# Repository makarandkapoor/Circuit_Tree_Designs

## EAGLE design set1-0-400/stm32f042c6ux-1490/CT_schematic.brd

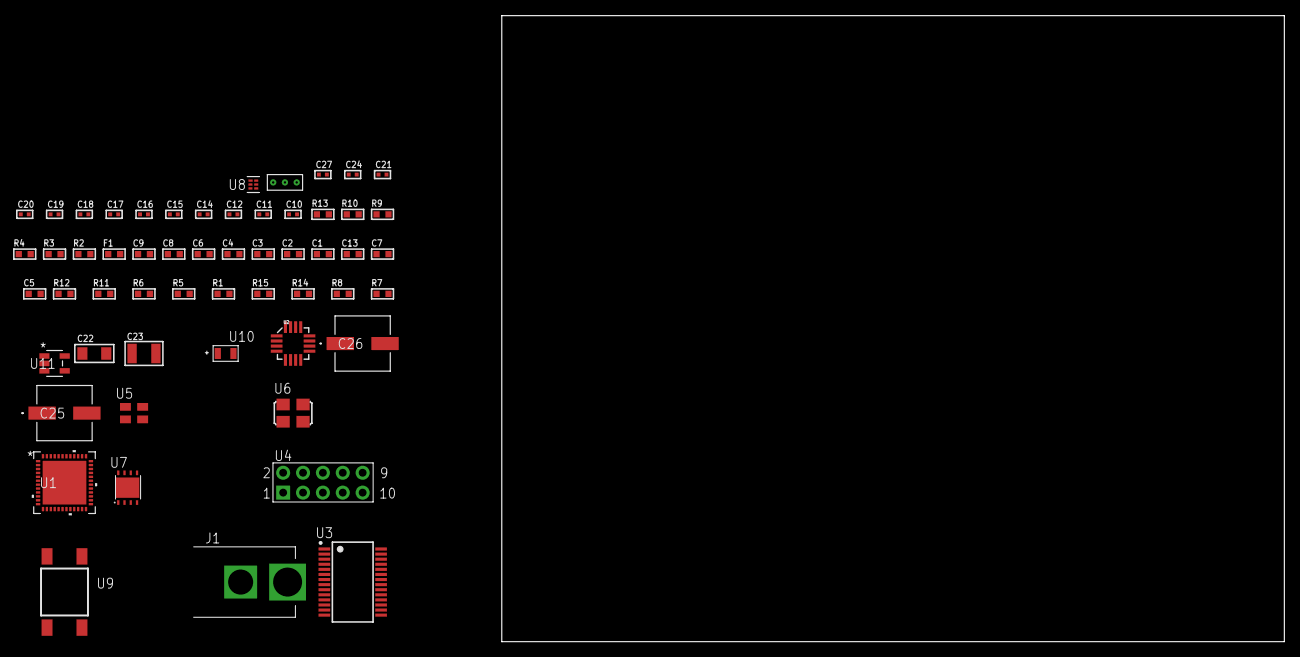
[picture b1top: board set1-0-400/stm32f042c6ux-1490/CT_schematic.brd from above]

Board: 2 copper layers, 100.0 x 80.0 mm, 56 parts (0 on the bottom side), 38 nets, no tracks yet.

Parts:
C1, C9: 1e-06; C0603
C2, C3, C4, C6: 1e-07; C0603
C5, C7: 4.7e-06; C0603
C8: 1e-08; C0603
C10, C11, C12, C19, C20, C21, C27: 1e-08; C0402
C13: 4.7e-07; C0603
C14, C15, C16, C17, C18, C24: 1e-07; C0402
C22: 1e-05; C1206
C23: 1e-05; C1210
C25, C26: 0.0001; EXV-9H
F1: 240.0; L0603
J1: PJ-037B; PJ-037B_PACKAGE
R1, R5, R6, R11, R12: 10000.0; R0603
R2, R10: 1000.0; R0603
R3: 1600.5; R0603
R4: 4700.0; R0603
R7, R8: 100000.0; R0603
R9: 2231.0; R0603
R13: 9100.0; R0603
R14: 680000.0; R0603
R15: 120000.0; R0603
U1: stm32f042c6u6; UFQFPN48
U2: l3g4200d; LGA-16
U3: ST3241EBPR; SSOP-28
U4: HTSS-105-01-G-D
U5: ASEK-32.768KHz-ECST; ASEK
U6: ASFL1-25MHZ-NCS; ASFL1
U7: LP3878SDX-ADJ/NOPB; WSON-8
U8: TPS3895ADRYR; SON-6
U9: 4-1437565-2; SW_4-1437565-2
U10: Q65110A2395; LGM67K-G1J2-24-Z
U11: nc7sz125m5x; NC7SZ125M5X
U12: Dummy; DUMMY_PACKAGE_122

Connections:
CLK_U1_3: U1.3, U5.3
CLK_U1_5: U1.5, U6.3
GND: C1.2, C2.2, C3.2, C4.2, C5.2, C6.2, C7.2, C8.2, C9.2, C10.2, C11.2, C12.2, C14.2, C17.2, C18.2, C19.2, C20.2, C21.2, C22.2, C23.2, C24.2, C25.2, C26.2, C27.2, J1.2, R2.2, R5.1, R5.2, R10.2, R13.2, R15.2, U1.8, U1.23, U1.35, U1.47, U1.49, U2.8, U2.9, U2.10, U2.11, U2.12, U2.13, U3.23, U3.25, U4.9, U5.2, U6.2, U7.3, U7.PAD, U8.2, U10.C, U11.1, U11.3, U12.1
NET_U1_7: R4.1, U1.7, U11.4
NET_U1_9: C8.1, C9.1, F1.1, U1.9
NET_U1_45: R3.1, U1.45, U10.A
NET_U1_46: R1.1, U1.46, U9.3, U9.4
NET_U2_14: C12.1, C13.1, U2.14
NET_U3_1: C16.1, U3.1
NET_U3_2: C16.2, U3.2
NET_U3_3: C18.1, U3.3
NET_U3_22: R7.1, U3.22
NET_U3_24: C15.2, U3.24
NET_U3_27: C17.1, U3.27
NET_U3_28: C15.1, U3.28
NET_U4_3: U3.4, U4.3
NET_U4_4: U3.5, U4.4
NET_U4_5: U3.9, U4.5
NET_U4_6: U3.10, U4.6
NET_U7_1: C21.1, U7.1
NET_U7_6: R9.2, R10.1, U7.6
NET_U7_8: R8.1, U7.8
NET_U8_1: R12.1, R13.1, U8.1
NET_U8_3: R14.2, R15.1, U8.3
NET_U8_4: R11.1, U8.4, U11.2
NET_U9_1: R2.1, U9.1, U9.2
PROC_SPI1_MISO: U1.16, U2.4
PROC_SPI1_MOSI: U1.17, U2.3
PROC_SPI1_NSS: R6.1, U1.14, U2.5
PROC_SPI1_SCK: U1.15, U2.2
PROC_TIM1_CH1: U1.29, U12.3
PROC_TIM1_CH2N: U1.18, U12.2
PROC_USART1_CTS: U1.32, U3.13
PROC_USART1_RTS: U1.33, U3.18
PROC_USART1_RX: U1.31, U3.19
PROC_USART1_TX: U1.30, U3.14
VCC_S1_8V6: C22.1, C25.1, C26.1, J1.1, R8.2, U7.4
VCC_TIER1_3V3: C1.1, C2.1, C3.1, C4.1, C5.1, C6.1, C7.1, C10.1, C11.1, C14.1, C19.1, C20.1, C23.1, C24.1, C27.1, F1.2, R1.2, R3.2, R4.2, R6.2, R7.2, R9.1, R11.2, R12.2, R14.1, U1.1, U1.24, U1.36, U1.48, U2.1, U2.15, U2.16, U3.26, U5.4, U6.4, U7.5, U8.6, U11.5

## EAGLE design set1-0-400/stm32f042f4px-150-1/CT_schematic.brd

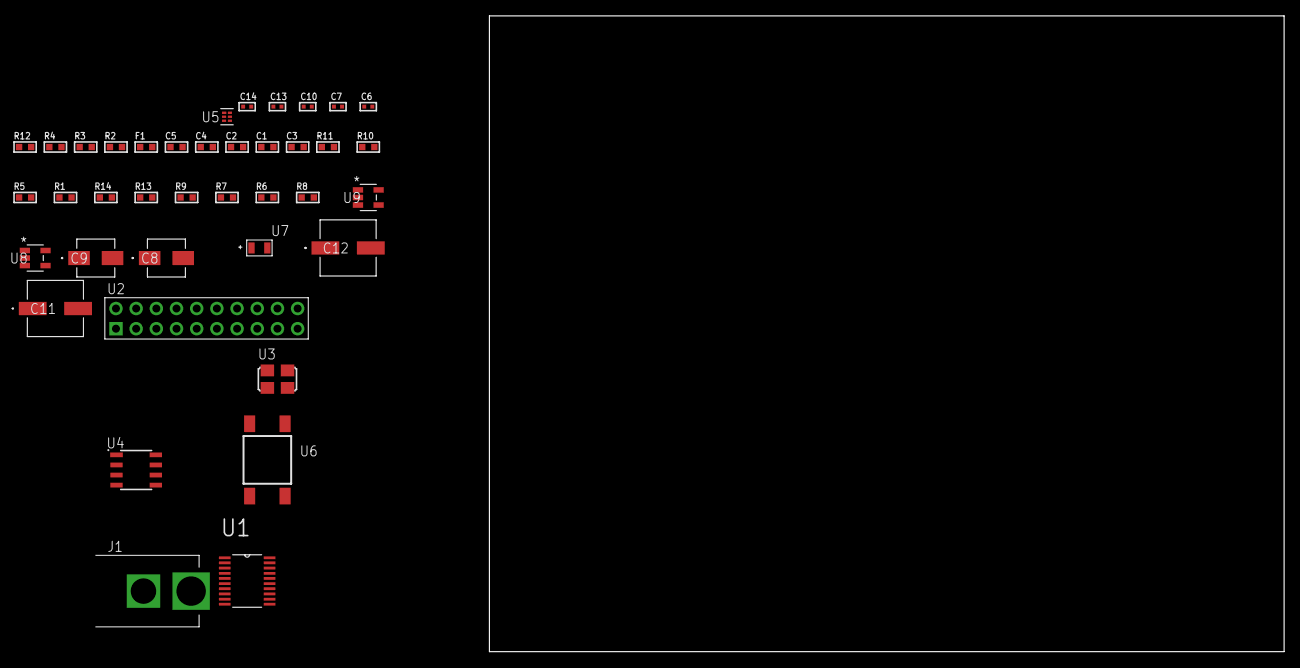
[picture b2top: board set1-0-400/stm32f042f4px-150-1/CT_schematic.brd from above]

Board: 2 copper layers, 100.0 x 80.0 mm, 39 parts (0 on the bottom side), 18 nets, no tracks yet.

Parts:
C1, C2: 1e-07; C0603
C3: 4.7e-06; C0603
C4: 1e-08; C0603
C5: 1e-06; C0603
C6, C10: 1e-07; C0402
C7, C13, C14: 1e-08; C0402
C8: 1e-06; EXV-9B
C9: 2.2e-06; EXV-9B
C11, C12: 0.0001; EXV-9H
F1: 240.0; L0603
J1: PJ-037B; PJ-037B_PACKAGE
R1, R5, R10, R11: 10000.0; R0603
R2: 1000.0; R0603
R3: 1600.5; R0603
R4: 4700.0; R0603
R6, R7, R9: 100000.0; R0603
R8: 164658.62; R0603
R12: 9100.0; R0603
R13: 680000.0; R0603
R14: 120000.0; R0603
U1: stm32f042f4p7; TSSOP20
U2: TST-110-05-T-D-RA
U3: ASFL1-25MHZ-NCS; ASFL1
U4: LP2954AIMX/NOPB; LP2954
U5: TPS3895ADRYR; SON-6
U6: 4-1437565-2; SW_4-1437565-2
U7: Q65110A2395; LGM67K-G1J2-24-Z
U8, U9: nc7sz125m5x; NC7SZ125M5X

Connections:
CLK_U1_2: U1.2, U3.3
GND: C1.2, C2.2, C3.2, C4.2, C5.2, C6.2, C7.2, C8.2, C9.2, C10.2, C11.2, C12.2, C13.2, C14.2, J1.2, R2.2, R9.2, R12.2, R14.2, U1.15, U2.4, U2.6, U2.8, U2.10, U2.12, U2.14, U2.16, U2.18, U2.20, U3.2, U4.4, U5.2, U7.C, U8.2, U8.3, U9.1, U9.3
NET_U1_4: R4.1, U1.4, U9.4
NET_U1_5: C4.1, C5.1, F1.1, U1.5
NET_U1_17: R3.1, U1.17, U7.A
NET_U1_18: R1.1, U1.18, U6.3, U6.4
NET_U4_3: R7.1, U4.3
NET_U4_5: R6.1, U4.5
NET_U4_7: R8.2, R9.1, U4.7
NET_U5_1: R11.1, R12.1, U5.1
NET_U5_3: R13.2, R14.1, U5.3
NET_U5_4: R10.1, U5.4, U8.4, U9.2
NET_U6_1: R2.1, U6.1, U6.2
PROC_SYS_SWCLK: U1.20, U2.9
PROC_SYS_SWDIO: U1.19, U2.7
RST_OUT_U2_SRESET_B: R5.1, U2.15, U8.1
VCC_S1_8V6: C8.1, C11.1, C12.1, J1.1, R7.2, U4.8
VCC_TIER1_3V3: C1.1, C2.1, C3.1, C6.1, C7.1, C9.1, C10.1, C13.1, C14.1, F1.2, R1.2, R3.2, R4.2, R5.2, R6.2, R8.1, R10.2, R11.2, R13.1, U1.16, U2.1, U3.4, U4.1, U5.6, U8.5, U9.5

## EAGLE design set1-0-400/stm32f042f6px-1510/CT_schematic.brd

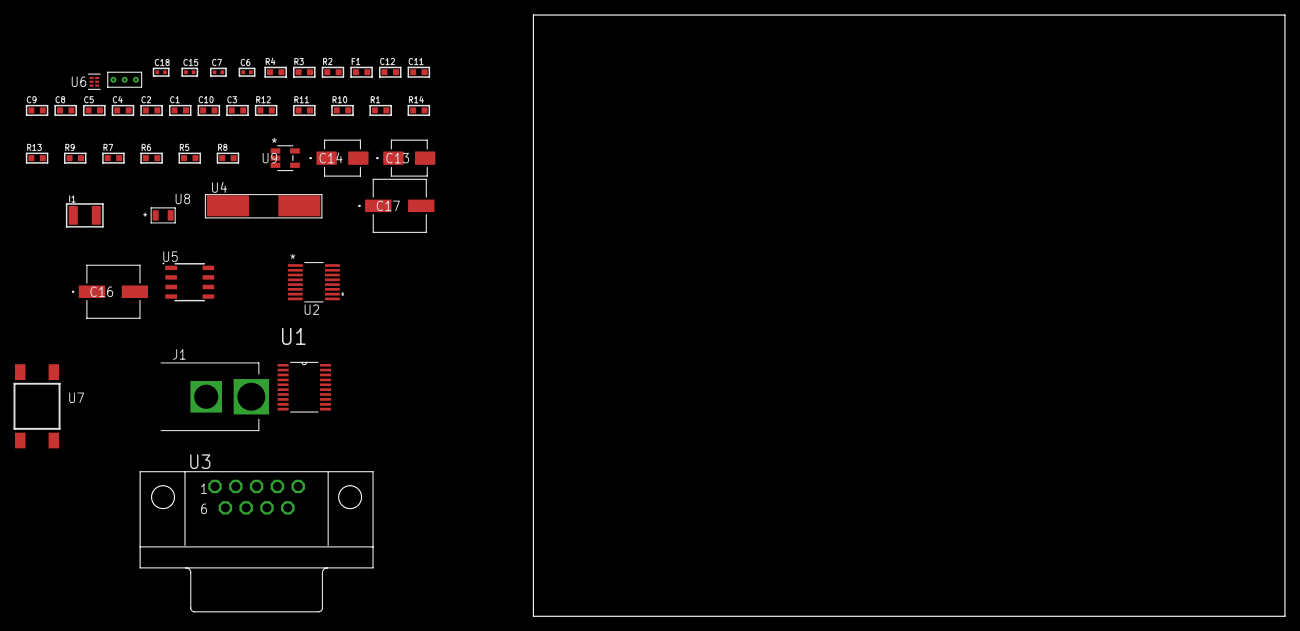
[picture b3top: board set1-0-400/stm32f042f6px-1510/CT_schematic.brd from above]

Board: 2 copper layers, 100.0 x 80.0 mm, 45 parts (0 on the bottom side), 29 nets, no tracks yet.

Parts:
C1, C2: 1e-07; C0603
C3: 4.7e-06; C0603
C4: 1e-08; C0603
C5, C8, C9, C11, C12: 1e-06; C0603
C6, C7: 1e-11; C0402
C10: 2.2e-07; C0603
C13: 1e-06; EXV-9B
C14: 2.2e-06; EXV-9B
C15: 1e-07; C0402
C16, C17: 0.0001; EXV-9H
C18: 1e-08; C0402
F1: 240.0; L0603
I1: 1e-05; L1210
J1: PJ-037B; PJ-037B_PACKAGE
R1, R10, R11: 10000.0; R0603
R2: 1000.0; R0603
R3: 1270.0; R0603
R4: 4700.0; R0603
R5, R6, R7, R9: 100000.0; R0603
R8: 101022.32; R0603
R12: 18000.0; R0603
R13: 470000.0; R0603
R14: 120000.0; R0603
U1: stm32f042f6p7; TSSOP20
U2: LTC2804CGN-1#PBF; SSOP-16
U3: 182-009-113R531; 182-009-MALE
U4: ABLS-25.000MHZ-B2F-T
U5: LP2954AIMX/NOPB; LP2954
U6: TPS3895ADRYR; SON-6
U7: 4-1437565-2; SW_4-1437565-2
U8: Q65110A2395; LGM67K-G1J2-24-Z
U9: nc7sz125m5x; NC7SZ125M5X
U10: Dummy; DUMMY_PACKAGE_89

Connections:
CLK_CRYSTAL_U1_2: C6.1, U1.2, U4.1
CLK_CRYSTAL_U1_3: C7.1, U1.3, U4.2
GND: C1.2, C2.2, C3.2, C4.2, C5.2, C6.2, C7.2, C8.2, C9.2, C11.2, C12.2, C13.2, C14.2, C15.2, C16.2, C17.2, C18.2, J1.2, R2.2, R9.2, R12.2, R14.2, U1.15, U2.8, U3.5, U5.4, U6.2, U8.C, U9.1, U9.3, U10.1
NET_U1_4: R4.1, U1.4, U9.4
NET_U1_5: C4.1, C5.1, F1.1, U1.5
NET_U1_19: R3.1, U1.19, U8.A
NET_U1_20: R1.1, U1.20, U7.3, U7.4
NET_U2_6: C8.1, U2.6
NET_U2_7: C10.1, I1.2, U2.7
NET_U2_9: C9.1, U2.9
NET_U2_10: C10.2, U2.10
NET_U2_11: R5.1, U2.11
NET_U3_2: U2.1, U3.2
NET_U3_3: U2.3, U3.3
NET_U3_7: U2.2, U3.7
NET_U3_8: U2.4, U3.8
NET_U5_3: R7.1, U5.3
NET_U5_5: R6.1, U5.5
NET_U5_7: R8.2, R9.1, U5.7
NET_U6_1: R11.1, R12.1, U6.1
NET_U6_3: R13.2, R14.1, U6.3
NET_U6_4: R10.1, U6.4, U9.2
NET_U7_1: R2.1, U7.1, U7.2
PROC_TIM1_CH1N: U1.13, U10.3
PROC_TIM1_CH3N: U1.14, U10.2
PROC_USART1_RX: U1.18, U2.16
PROC_USART1_TX: U1.17, U2.14
VCC_S1_13V6: C13.1, C16.1, C17.1, J1.1, R7.2, U5.8
VCC_TIER1_2V5: C1.1, C2.1, C3.1, C11.1, C12.1, C14.1, C15.1, C18.1, F1.2, I1.1, R1.2, R3.2, R4.2, R5.2, R6.2, R8.1, R10.2, R11.2, R13.1, U1.16, U2.5, U2.12, U5.1, U6.6, U9.5

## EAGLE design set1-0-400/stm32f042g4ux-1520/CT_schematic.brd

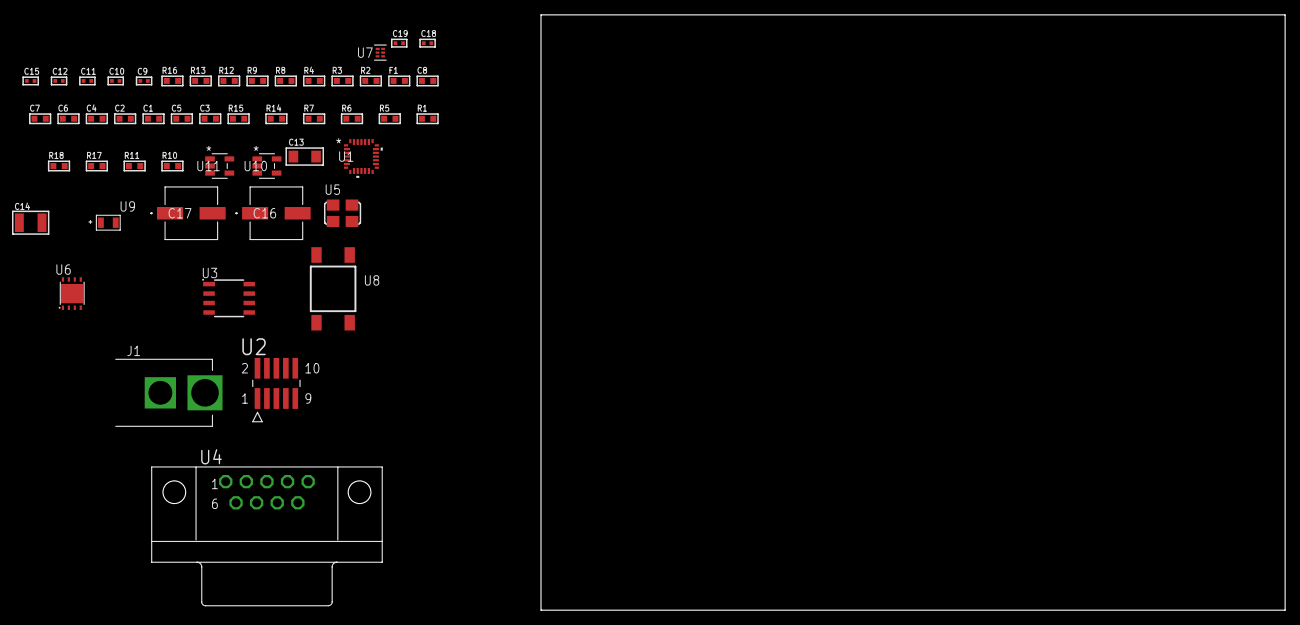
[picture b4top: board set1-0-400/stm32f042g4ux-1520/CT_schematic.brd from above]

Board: 2 copper layers, 100.0 x 80.0 mm, 50 parts (0 on the bottom side), 24 nets, no tracks yet.

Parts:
C1, C2, C4: 1e-07; C0603
C3, C5: 4.7e-06; C0603
C6, C7: 1e-08; C0603
C8: 1e-06; C0603
C9, C10, C15: 1e-07; C0402
C11, C12, C18, C19: 1e-08; C0402
C13: 1e-05; C1206
C14: 1e-05; C1210
C16, C17: 0.0001; EXV-9H
F1: 240.0; L0603
J1: PJ-037B; PJ-037B_PACKAGE
R1, R5, R6, R7, R14, R15: 10000.0; R0603
R2, R13: 1000.0; R0603
R3: 1600.5; R0603
R4: 4700.0; R0603
R8: 5.0; R0603
R9: 120.0; R0603
R10, R11: 100000.0; R0603
R12: 2231.0; R0603
R16: 9100.0; R0603
R17: 680000.0; R0603
R18: 120000.0; R0603
U1: stm32f042g4u7; UFQFPN28
U2: FTSH-105-01-L-DV-K; SAMTEC_FTSH-105-01-L-DV-K
U3: SN65HVD230D; SOIC-8
U4: 182-009-113R531; 182-009-MALE
U5: ASFL1-25MHZ-NCS; ASFL1
U6: LP3878SDX-ADJ/NOPB; WSON-8
U7: TPS3895ADRYR; SON-6
U8: 4-1437565-2; SW_4-1437565-2
U9: Q65110A2395; LGM67K-G1J2-24-Z
U10, U11: nc7sz125m5x; NC7SZ125M5X

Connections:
CLK_U1_2: U1.2, U5.3
GND: C1.2, C2.2, C3.2, C4.2, C5.2, C6.2, C7.2, C8.2, C9.2, C10.2, C11.2, C12.2, C13.2, C14.2, C15.2, C16.2, C17.2, C18.2, C19.2, J1.2, R2.2, R8.2, R10.2, R13.2, R16.2, R18.2, U1.16, U2.3, U2.5, U3.2, U4.5, U5.2, U6.3, U6.PAD, U7.2, U9.C, U10.2, U10.3, U11.1, U11.3
NET_U1_4: R4.1, U1.4, U11.4
NET_U1_5: C6.1, C7.1, C8.1, F1.1, U1.5
NET_U1_27: R3.1, U1.27, U9.A
NET_U1_28: R1.1, U1.28, U8.3, U8.4
NET_U2_9: R8.1, U2.9
NET_U3_6: R9.2, U3.6
NET_U3_8: R10.1, U3.8
NET_U4_2: R9.2, U3.6, U4.2
NET_U4_3: R9.1, U3.7, U4.3
NET_U6_1: C12.1, U6.1
NET_U6_6: R12.2, R13.1, U6.6
NET_U6_8: R11.1, U6.8
NET_U7_1: R15.1, R16.1, U7.1
NET_U7_3: R17.2, R18.1, U7.3
NET_U7_4: R14.1, U7.4, U10.4, U11.2
NET_U8_1: R2.1, U8.1, U8.2
PROC_CAN_RX: U1.1, U3.4
PROC_SYS_SWCLK: R6.1, U1.22, U2.4
PROC_SYS_SWDIO: R7.1, U1.21, U2.2
RST_OUT_U2_JTAG_RST_B: R5.1, U2.10, U10.1
VCC_S1_11V1: C13.1, C16.1, C17.1, J1.1, R11.2, U6.4
VCC_TIER1_3V3: C1.1, C2.1, C3.1, C4.1, C5.1, C9.1, C10.1, C11.1, C14.1, C15.1, C18.1, C19.1, F1.2, R1.2, R3.2, R4.2, R5.2, R6.2, R7.2, R12.1, R14.2, R15.2, R17.1, U1.17, U1.18, U2.1, U3.3, U5.4, U6.5, U7.6, U10.5, U11.5

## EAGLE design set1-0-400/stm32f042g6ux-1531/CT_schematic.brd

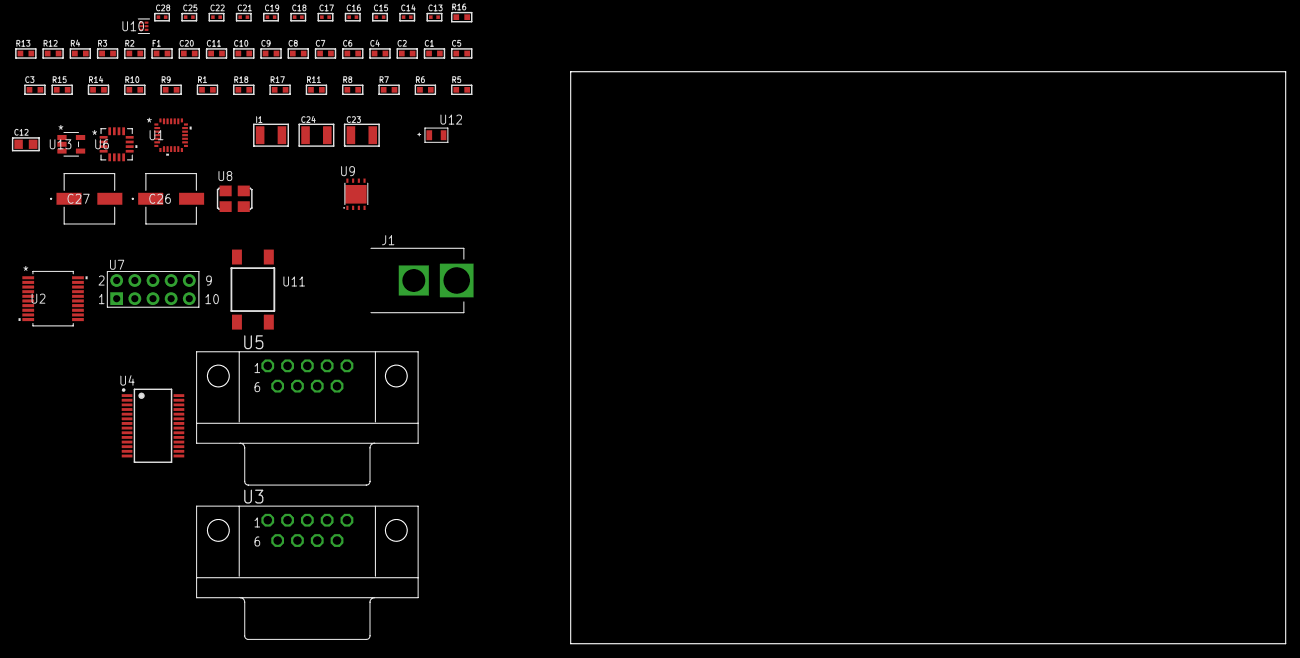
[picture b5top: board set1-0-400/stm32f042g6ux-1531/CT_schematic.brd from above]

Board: 2 copper layers, 100.0 x 80.0 mm, 62 parts (0 on the bottom side), 53 nets, no tracks yet.

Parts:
C1, C2, C4: 1e-07; C0603
C3, C5: 4.7e-06; C0603
C6, C7: 1e-08; C0603
C8, C9, C10, C11, C20: 1e-06; C0603
C12: 4.7e-06; C0805
C13, C14, C15, C16, C17, C18, C19, C25: 1e-07; C0402
C21, C22, C28: 1e-08; C0402
C23, C24: 1e-05; C1210
C26, C27: 0.0001; EXV-9H
F1: 240.0; L0603
I1: 1.5e-05; L1210
J1: PJ-037B; PJ-037B_PACKAGE
R1, R9, R10, R14, R15: 10000.0; R0603
R2, R13: 1000.0; R0603
R3: 1600.5; R0603
R4: 4700.0; R0603
R5, R6, R7, R8, R11: 100000.0; R0603
R12: 2231.0; R0603
R16: 9100.0; R0603
R17: 680000.0; R0603
R18: 120000.0; R0603
U1: stm32f042g6u6; UFQFPN28
U2: MAX3218EAP+T; SSOP-20
U3, U5: 182-009-113R531; 182-009-MALE
U4: ST3241EBPR; SSOP-28
U6: TSC2046IRGVR; VQFN-16
U7: HTSS-105-01-G-D
U8: ASFL1-25MHZ-NCS; ASFL1
U9: LP3878SDX-ADJ/NOPB; WSON-8
U10: TPS3895ADRYR; SON-6
U11: 4-1437565-2; SW_4-1437565-2
U12: Q65110A2395; LGM67K-G1J2-24-Z
U13: nc7sz125m5x; NC7SZ125M5X

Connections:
CLK_U1_2: U1.2, U8.3
GND: C1.2, C2.2, C3.2, C4.2, C5.2, C6.2, C7.2, C8.2, C9.2, C10.2, C11.2, C13.2, C16.2, C17.2, C18.2, C19.2, C20.2, C21.2, C22.2, C23.2, C24.2, C25.2, C26.2, C27.2, C28.2, J1.2, R2.2, R13.2, R16.2, R18.2, U1.16, U2.5, U2.17, U2.20, U3.5, U4.23, U4.25, U5.5, U6.10, U7.9, U8.2, U9.3, U9.PAD, U10.2, U12.C, U13.1, U13.3
NET_U1_4: R4.1, U1.4, U13.4
NET_U1_5: C6.1, C7.1, C8.1, F1.1, U1.5
NET_U1_27: R3.1, U1.27, U12.A
NET_U1_28: R1.1, U1.28, U11.3, U11.4
NET_U2_1: I1.1, U2.1
NET_U2_2: R5.1, U2.2
NET_U2_3: R6.1, U2.3
NET_U2_4: R7.1, U2.4
NET_U2_15: C11.1, U2.15
NET_U2_16: C12.2, U2.16
NET_U2_18: C12.1, U2.18
NET_U2_19: C10.1, U2.19
NET_U3_2: U2.12, U3.2
NET_U3_3: U2.14, U3.3
NET_U3_7: U2.11, U3.7
NET_U3_8: U2.13, U3.8
NET_U4_1: C15.1, U4.1
NET_U4_2: C15.2, U4.2
NET_U4_3: C17.1, U4.3
NET_U4_22: R8.1, U4.22
NET_U4_24: C14.2, U4.24
NET_U4_27: C16.1, U4.27
NET_U4_28: C14.1, U4.28
NET_U5_2: U4.4, U5.2
NET_U5_3: U4.9, U5.3
NET_U5_7: U4.5, U5.7
NET_U5_8: U4.10, U5.8
NET_U6_15: R10.1, U6.15
NET_U7_3: U6.7, U7.3
NET_U7_4: U6.9, U7.4
NET_U7_5: U6.6, U7.5
NET_U7_6: U6.8, U7.6
NET_U9_1: C22.1, U9.1
NET_U9_6: R12.2, R13.1, U9.6
NET_U9_8: R11.1, U9.8
NET_U10_1: R15.1, R16.1, U10.1
NET_U10_3: R17.2, R18.1, U10.3
NET_U10_4: R14.1, U10.4, U13.2
NET_U11_1: R2.1, U11.1, U11.2
PROC_SPI1_MISO: U1.12, U6.16
PROC_SPI1_MOSI: U1.13, U6.2
PROC_SPI1_NSS: R9.1, U1.10, U6.3
PROC_SPI1_SCK: U1.11, U6.4
PROC_USART1_RX: U1.20, U4.19
PROC_USART1_TX: U1.19, U4.14
PROC_USART2_CTS: U1.6, U2.8
PROC_USART2_RTS: U1.7, U2.10
PROC_USART2_RX: U1.9, U2.9
PROC_USART2_TX: U1.8, U2.7
VCC_S1_14V8: C23.1, C26.1, C27.1, J1.1, R11.2, U9.4
VCC_TIER1_3V3: C1.1, C2.1, C3.1, C4.1, C5.1, C9.1, C13.1, C18.1, C19.1, C20.1, C21.1, C24.1, C25.1, C28.1, F1.2, I1.2, R1.2, R3.2, R4.2, R5.2, R6.2, R7.2, R8.2, R9.2, R10.2, R12.1, R14.2, R15.2, R17.1, U1.17, U1.18, U2.6, U4.26, U6.5, U6.14, U8.4, U9.5, U10.6, U13.5

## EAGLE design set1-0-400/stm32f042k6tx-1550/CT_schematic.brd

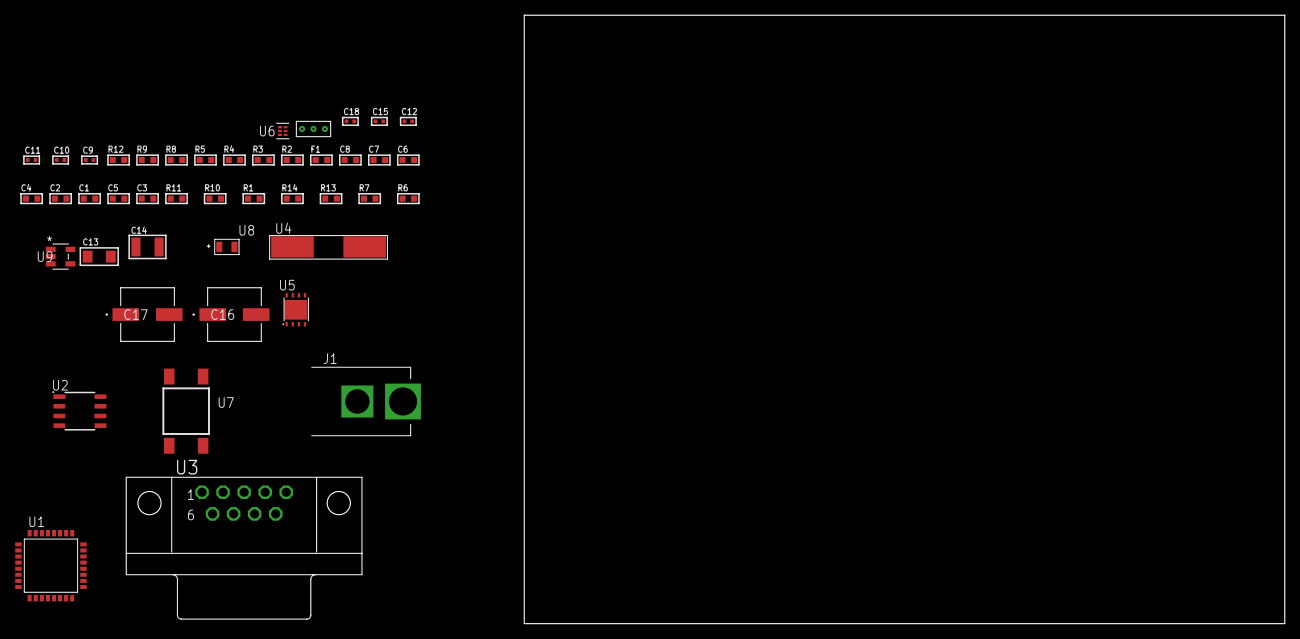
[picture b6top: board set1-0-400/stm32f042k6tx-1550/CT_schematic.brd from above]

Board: 2 copper layers, 100.0 x 80.0 mm, 44 parts (0 on the bottom side), 24 nets, no tracks yet.

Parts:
C1, C2, C4: 1e-07; C0603
C3, C5: 4.7e-06; C0603
C6, C7: 1e-08; C0603
C8: 1e-06; C0603
C9, C10: 1e-11; C0402
C11, C15: 1e-07; C0402
C12, C18: 1e-08; C0402
C13: 1e-05; C1206
C14: 1e-05; C1210
C16, C17: 0.0001; EXV-9H
F1: 240.0; L0603
J1: PJ-037B; PJ-037B_PACKAGE
R1, R10, R11: 10000.0; R0603
R2, R9: 1000.0; R0603
R3: 1600.5; R0603
R4: 4700.0; R0603
R5: 120.0; R0603
R6: 470000.0; R0603
R7: 100000.0; R0603
R8: 2231.0; R0603
R12: 9100.0; R0603
R13: 680000.0; R0603
R14: 120000.0; R0603
U1: stm32f042k6t7; LQFP32
U2: SN65HVD230D; SOIC-8
U3: 182-009-113R531; 182-009-MALE
U4: ABLS-25.000MHZ-B2F-T
U5: LP3878SDX-ADJ/NOPB; WSON-8
U6: TPS3895ADRYR; SON-6
U7: 4-1437565-2; SW_4-1437565-2
U8: Q65110A2395; LGM67K-G1J2-24-Z
U9: nc7sz125m5x; NC7SZ125M5X
U10: Dummy; DUMMY_PACKAGE_87

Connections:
CLK_CRYSTAL_U1_2: C9.1, U1.2, U4.1
CLK_CRYSTAL_U1_3: C10.1, U1.3, U4.2
GND: C1.2, C2.2, C3.2, C4.2, C5.2, C6.2, C7.2, C8.2, C9.2, C10.2, C11.2, C12.2, C13.2, C14.2, C15.2, C16.2, C17.2, C18.2, J1.2, R2.2, R6.2, R9.2, R12.2, R14.2, U1.16, U1.32, U2.2, U3.5, U5.3, U5.PAD, U6.2, U8.C, U9.1, U9.3, U10.1
NET_U1_4: R4.1, U1.4, U9.4
NET_U1_5: C6.1, C7.1, C8.1, F1.1, U1.5
NET_U1_30: R3.1, U1.30, U8.A
NET_U1_31: R1.1, U1.31, U7.3, U7.4
NET_U2_6: R5.2, U2.6
NET_U2_8: R6.1, U2.8
NET_U3_2: R5.2, U2.6, U3.2
NET_U3_3: R5.1, U2.7, U3.3
NET_U5_1: C12.1, U5.1
NET_U5_6: R8.2, R9.1, U5.6
NET_U5_8: R7.1, U5.8
NET_U6_1: R11.1, R12.1, U6.1
NET_U6_3: R13.2, R14.1, U6.3
NET_U6_4: R10.1, U6.4, U9.2
NET_U7_1: R2.1, U7.1, U7.2
PROC_CAN_RX: U1.21, U2.4
PROC_CAN_TX: U1.22, U2.1
PROC_PA0: U1.6, U10.2
PROC_PA1: U1.7, U10.3
VCC_S1_9V7: C13.1, C16.1, C17.1, J1.1, R7.2, U5.4
VCC_TIER1_3V3: C1.1, C2.1, C3.1, C4.1, C5.1, C11.1, C14.1, C15.1, C18.1, F1.2, R1.2, R3.2, R4.2, R8.1, R10.2, R11.2, R13.1, U1.1, U1.17, U2.3, U5.5, U6.6, U9.5

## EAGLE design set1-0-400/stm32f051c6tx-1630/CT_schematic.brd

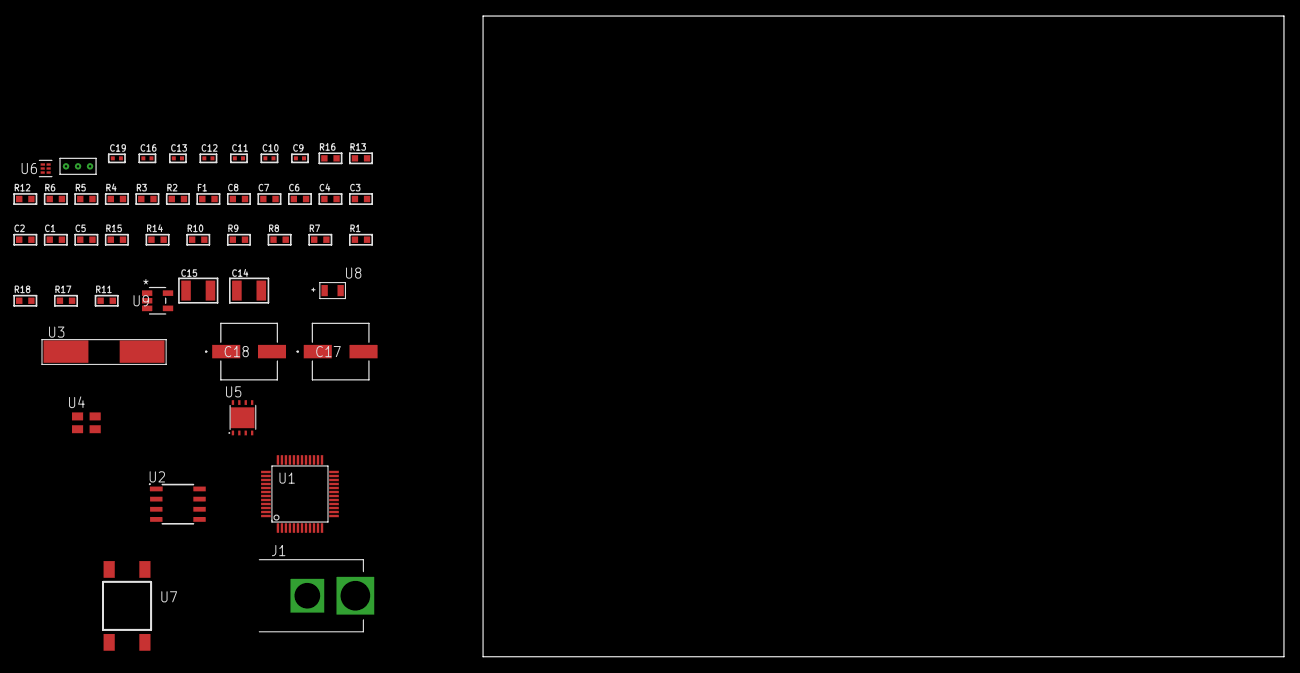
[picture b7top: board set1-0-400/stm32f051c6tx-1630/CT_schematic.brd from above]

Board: 2 copper layers, 100.0 x 80.0 mm, 49 parts (0 on the bottom side), 25 nets, no tracks yet.

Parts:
C1, C8: 1e-06; C0603
C2, C3, C4, C6: 1e-07; C0603
C5: 4.7e-06; C0603
C7: 1e-08; C0603
C9, C10: 1e-11; C0402
C11, C12, C13, C19: 1e-08; C0402
C14, C15: 1e-05; C1210
C16: 1e-07; C0402
C17, C18: 0.0001; EXV-9H
F1: 240.0; L0603
J1: PJ-037B; PJ-037B_PACKAGE
R1, R7, R8, R9, R10, R14, R15: 10000.0; R0603
R2, R13: 1000.0; R0603
R3: 1600.5; R0603
R4: 4700.0; R0603
R5, R6: 2200.0; R0603
R11: 100000.0; R0603
R12: 2231.0; R0603
R16: 9100.0; R0603
R17: 680000.0; R0603
R18: 120000.0; R0603
U1: stm32f051c6t7; LQFP48
U2: 24AA1025T-I/SN; SOIC-8
U3: ABLS-25.000MHZ-B2F-T
U4: ASEK-32.768KHz-ECST; ASEK
U5: LP3878SDX-ADJ/NOPB; WSON-8
U6: TPS3895ADRYR; SON-6
U7: 4-1437565-2; SW_4-1437565-2
U8: Q65110A2395; LGM67K-G1J2-24-Z
U9: nc7sz125m5x; NC7SZ125M5X
U10: Dummy; DUMMY_PACKAGE_100

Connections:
CLK_CRYSTAL_U1_5: C9.1, U1.5, U3.1
CLK_CRYSTAL_U1_6: C10.1, U1.6, U3.2
CLK_U1_3: U1.3, U4.3
GND: C1.2, C2.2, C3.2, C4.2, C5.2, C6.2, C7.2, C8.2, C9.2, C10.2, C11.2, C12.2, C13.2, C14.2, C15.2, C16.2, C17.2, C18.2, C19.2, J1.2, R2.2, R7.2, R9.2, R13.2, R16.2, R18.2, U1.8, U1.23, U1.47, U2.4, U2.7, U4.2, U5.3, U5.PAD, U6.2, U8.C, U9.1, U9.3, U10.1
NET_U1_7: R4.1, U1.7, U9.4
NET_U1_9: C7.1, C8.1, F1.1, U1.9
NET_U1_42: R5.1, U1.42, U2.6
NET_U1_43: R6.1, U1.43, U2.5
NET_U1_44: R7.1, U1.44
NET_U1_45: R3.1, U1.45, U8.A
NET_U1_46: R1.1, U1.46, U7.3, U7.4
NET_U2_1: R9.1, U2.1
NET_U2_2: R10.1, U2.2
NET_U2_3: R8.1, U2.3
NET_U5_1: C13.1, U5.1
NET_U5_6: R12.2, R13.1, U5.6
NET_U5_8: R11.1, U5.8
NET_U6_1: R15.1, R16.1, U6.1
NET_U6_3: R17.2, R18.1, U6.3
NET_U6_4: R14.1, U6.4, U9.2
NET_U7_1: R2.1, U7.1, U7.2
PROC_TIM1_CH2: U1.30, U10.2
PROC_TIM1_CH4: U1.32, U10.3
VCC_S1_14V2: C14.1, C17.1, C18.1, J1.1, R11.2, U5.4
VCC_TIER1_3V3: C1.1, C2.1, C3.1, C4.1, C5.1, C6.1, C11.1, C12.1, C15.1, C16.1, C19.1, F1.2, R1.2, R3.2, R4.2, R5.2, R6.2, R8.2, R10.2, R12.1, R14.2, R15.2, R17.1, U1.1, U1.24, U1.48, U2.8, U4.4, U5.5, U6.6, U9.5

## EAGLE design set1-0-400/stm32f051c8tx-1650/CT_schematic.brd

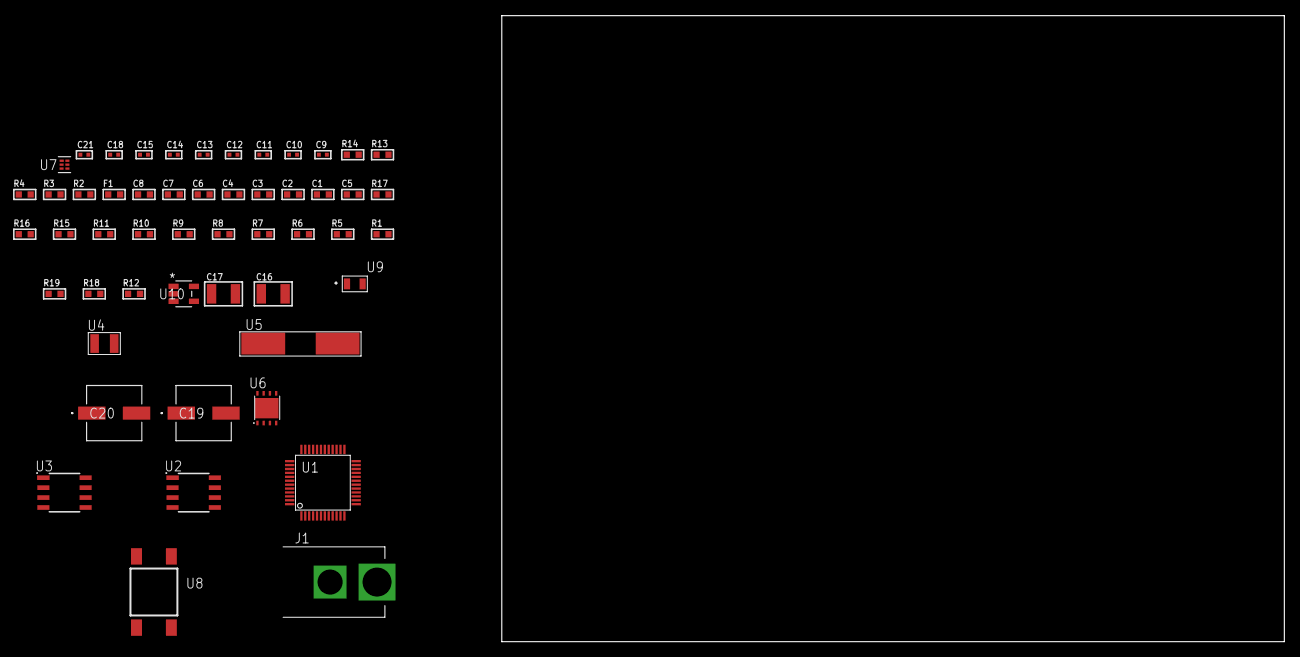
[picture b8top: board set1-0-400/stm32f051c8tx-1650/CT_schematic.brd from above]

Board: 2 copper layers, 100.0 x 80.0 mm, 52 parts (0 on the bottom side), 31 nets, no tracks yet.

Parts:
C1, C8: 1e-06; C0603
C2, C3, C4, C6: 1e-07; C0603
C5: 4.7e-06; C0603
C7: 1e-08; C0603
C9, C10, C11, C12: 1e-11; C0402
C13, C14, C15, C21: 1e-08; C0402
C16, C17: 1e-05; C1210
C18: 1e-07; C0402
C19, C20: 0.0001; EXV-9H
F1: 240.0; L0603
J1: PJ-037B; PJ-037B_PACKAGE
R1, R5, R6, R7, R8, R9, R10, R11, R15, R16: 10000.0; R0603
R2, R14: 1000.0; R0603
R3: 1270.0; R0603
R4: 4700.0; R0603
R12: 100000.0; R0603
R13: 1500.0; R0603
R17: 18000.0; R0603
R18: 470000.0; R0603
R19: 120000.0; R0603
U1: stm32f051c8t6; LQFP48
U2, U3: AT25160B-SSHL-T; SOIC-8
U4: ABS07-32.768KHZ-7-T
U5: ABLS-25.000MHZ-B2F-T
U6: LP3878SDX-ADJ/NOPB; WSON-8
U7: TPS3895ADRYR; SON-6
U8: 4-1437565-2; SW_4-1437565-2
U9: Q65110A2395; LGM67K-G1J2-24-Z
U10: nc7sz125m5x; NC7SZ125M5X

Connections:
CLK_CRYSTAL_U1_3: C9.1, U1.3, U4.1
CLK_CRYSTAL_U1_4: C10.1, U1.4, U4.2
CLK_CRYSTAL_U1_5: C11.1, U1.5, U5.1
CLK_CRYSTAL_U1_6: C12.1, U1.6, U5.2
GND: C1.2, C2.2, C3.2, C4.2, C5.2, C6.2, C7.2, C8.2, C9.2, C10.2, C11.2, C12.2, C13.2, C14.2, C15.2, C16.2, C17.2, C18.2, C19.2, C20.2, C21.2, J1.2, R2.2, R5.2, R14.2, R17.2, R19.2, U1.8, U1.23, U1.47, U2.4, U3.4, U6.3, U6.PAD, U7.2, U9.C, U10.1, U10.3
NET_U1_7: R4.1, U1.7, U10.4
NET_U1_9: C7.1, C8.1, F1.1, U1.9
NET_U1_44: R5.1, U1.44
NET_U1_45: R3.1, U1.45, U9.A
NET_U1_46: R1.1, U1.46, U8.3, U8.4
NET_U2_3: R6.1, U2.3
NET_U2_7: R8.1, U2.7
NET_U3_3: R9.1, U3.3
NET_U3_7: R11.1, U3.7
NET_U6_1: C15.1, U6.1
NET_U6_6: R13.2, R14.1, U6.6
NET_U6_8: R12.1, U6.8
NET_U7_1: R16.1, R17.1, U7.1
NET_U7_3: R18.2, R19.1, U7.3
NET_U7_4: R15.1, U7.4, U10.2
NET_U8_1: R2.1, U8.1, U8.2
PROC_SPI1_MISO: U1.16, U2.2
PROC_SPI1_MOSI: U1.17, U2.5
PROC_SPI1_NSS: R7.1, U1.14, U2.1
PROC_SPI1_SCK: U1.15, U2.6
PROC_SPI2_MISO: U1.27, U3.2
PROC_SPI2_MOSI: U1.28, U3.5
PROC_SPI2_NSS: R10.1, U1.25, U3.1
PROC_SPI2_SCK: U1.26, U3.6
VCC_S1_14V7: C16.1, C19.1, C20.1, J1.1, R12.2, U6.4
VCC_TIER1_2V5: C1.1, C2.1, C3.1, C4.1, C5.1, C6.1, C13.1, C14.1, C17.1, C18.1, C21.1, F1.2, R1.2, R3.2, R4.2, R6.2, R7.2, R8.2, R9.2, R10.2, R11.2, R13.1, R15.2, R16.2, R18.1, U1.1, U1.24, U1.48, U2.8, U3.8, U6.5, U7.6, U10.5
